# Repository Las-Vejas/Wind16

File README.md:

# Wind16
A 4x4 macropad, with backlit keys and a fully square design.

## Components

The macropad contains 16 keys, each backlit with an SK6812mini-e led. It is controlled by a Seeed XIAO RP2040 microcontroller using either kmk or qmk software.
The switches will be Gateron Milky Yellows as they feel magnificent. On them there will be white keycaps on which I will make vynil stickers for when I decide on the actions that the keys will be doing.

A lot of people on the HackClub Slack have been against my design, and how I have placed the Xiao. I myself think its a great design choice, that won’t interfere with any other component because, in theory with pin headers commonly being 2 mm tall, I should have enough clearance to fit my components on the top and bottom part of the pcb with just enough to spare so that the RP2040 wouldn’t be touching anything.

<br>

<br>

<br>

<br>

## BOM

| **Quantity** | **Item**                      | **Cost** | **Link**                                                                                                                                                                                                                                                                                                                                                                                                                                                                                                                                                                                                                             |
| ------------ | ----------------------------- | -------- | ------------------------------------------------------------------------------------------------------------------------------------------------------------------------------------------------------------------------------------------------------------------------------------------------------------------------------------------------------------------------------------------------------------------------------------------------------------------------------------------------------------------------------------------------------------------------------------------------------------------------------------ |
| 16           | Gateron Milky Yellow Switches | $8.32    | [Link](https://fr.aliexpress.com/item/1005006425450443.html?spm=a2g0o.cart.0.0.565438danX8OTX&mp=1&pdp_npi=5%40dis%21USD%21USD%208.32%21USD%208.32%21%21USD%208.32%21%21%21%40211b819117572797256232729e57a1%2112000037120671470%21ct%21LU%216401819456%21%211%210&gatewayAdapt=glo2fra) |
| 16           | Diodes SOD-123                | $1.56    | [Link](https://fr.aliexpress.com/item/1005001994794541.html?spm=a2g0o.order_detail.order_detail_item.3.e827f19ctnbrt6&gatewayAdapt=glo2fra) |
| 16           | SK6812mini-e Leds             | $3.33    | [Link](https://fr.aliexpress.com/item/1005003056797785.html?spm=a2g0o.detail.0.0.21a3YgQUYgQUyJ&mp=1&pdp_npi=5%40dis%21USD%21USD%204.76%21USD%203.33%21%21USD%203.26%21%21%21%40211b819117572793994331848e57a1%2112000023624298356%21ct%21LU%216401819456%21%211%210&_gl=1*wax1qx*_gcl_au*MTMyNTE0ODE3My4xNzUxNTY4NzEw*_ga*OTU2MTIwNzcxMDc0MTcyLjE3NTEwOTE0NzQ2NDg.*_ga_VED1YSGNC7*czE3NTcyNzkxNzkkbzQyJGcxJHQxNzU3Mjc5Mzk5JGo1JGwwJGgw&gatewayAdapt=glo2fra) |
| 1            | Seeed Xiao RP2040             | $8.75    | [Link](https://fr.aliexpress.com/item/1005003682505451.html?spm=a2g0o.productlist.main.1.29f17691lODYnp&algo_pvid=3de96513-9bd7-44e5-bd78-c8e1c5994e89&algo_exp_id=3de96513-9bd7-44e5-bd78-c8e1c5994e89-0&pdp_ext_f=%7B%22order%22%3A%2240%22%2C%22eval%22%3A%221%22%7D&pdp_npi=6%40dis%21EUR%217.28%214.52%21%21%218.30%215.15%21%402103868817572792142017471ef2af%2112000040089549450%21sea%21LU%216401819456%21X%211%210%21n_tag%3A-29912%3Bd%3A538c1a44%3Bm03_new_user%3A-29895&curPageLogUid=zx985QJAQOHJ&utparam-url=scene%3Asearch%7Cquery_from%3A%7Cx_object_id%3A1005003682505451%7C_p_origin_prod%3A&gatewayAdapt=glo2fra) |
| 16           | See-through keycaps           | $8.28    | [Link](https://fr.aliexpress.com/item/1005002976015114.html?spm=a2g0o.cart.0.0.59b138da7fjJ33&mp=1&pdp_npi=5%40dis%21USD%21USD%204.14%21USD%204.14%21%21USD%203.94%21%21%21%40211b876e17572803462205417e89b4%2112000023033844982%21ct%21LU%216401819456%21%212%210&gatewayAdapt=glo2fra) |
| 1            | 3D printed case               | N/A      | N/A  |                                                                                                                                                                                                                                                                                                                                                                                                                                                                                                                                                                                                                                
| 5            | M2 6mm Screws                 | $1.70    | [Link](https://www.aliexpress.com/item/1005004531602992.html?spm=a2g0o.cart.0.0.3b7738dao8IXAl&mp=1&pdp_npi=5%40dis%21USD%21USD%201.76%21USD%201.70%21%21USD%201.61%21%21%21%402103890917573922922277800e2784%2112000029499545502%21ct%21LU%216401819456%21%211%210&pdp_ext_f=%7B%22cart2PdpParams%22%3A%7B%22pdpBusinessMode%22%3A%22retail%22%7D%7D) |                                                                                                                                                                                                                                                                                                                                                                                                                                                                                                                                                                                                                                 | 5            | M2 8mm Standoffs              | $3.99    | [Link](https://www.aliexpress.com/item/32974970926.html?spm=a2g0o.cart.0.0.3b7738dao8IXAl&mp=1&pdp_npi=5%40dis%21USD%21USD%203.19%21USD%203.03%21%21USD%202.97%21%21%21%402103890917573923781348484e2784%2166700945881%21ct%21LU%216401819456%21%211%210) |
| 5            | M2 8mm Standoffs              | $3.30    | [Link](https://www.aliexpress.com/item/32974970926.html?spm=a2g0o.cart.0.0.f8e638daTMm8RF&mp=1&pdp_npi=5%40dis%21USD%21USD%203.19%21USD%203.03%21%21USD%203.03%21%21%21%402103835c17574519186483243e8d53%2166700945881%21ct%21LU%216401819456%21%211%210) |
| 5            | Rubber Bumpers (feet)         | $4.01    | [Link](https://fr.aliexpress.com/item/1005006259472984.html?spm=a2g0o.cart.0.0.3b7738dao8IXAl&mp=1&pdp_npi=5%40dis%21USD%21USD%202.77%21USD%202.77%21%21USD%202.77%21%21%21%402103890917573922922277800e2784%2112000036504769044%21ct%21LU%216401819456%21%211%210&gatewayAdapt=glo2fra) |

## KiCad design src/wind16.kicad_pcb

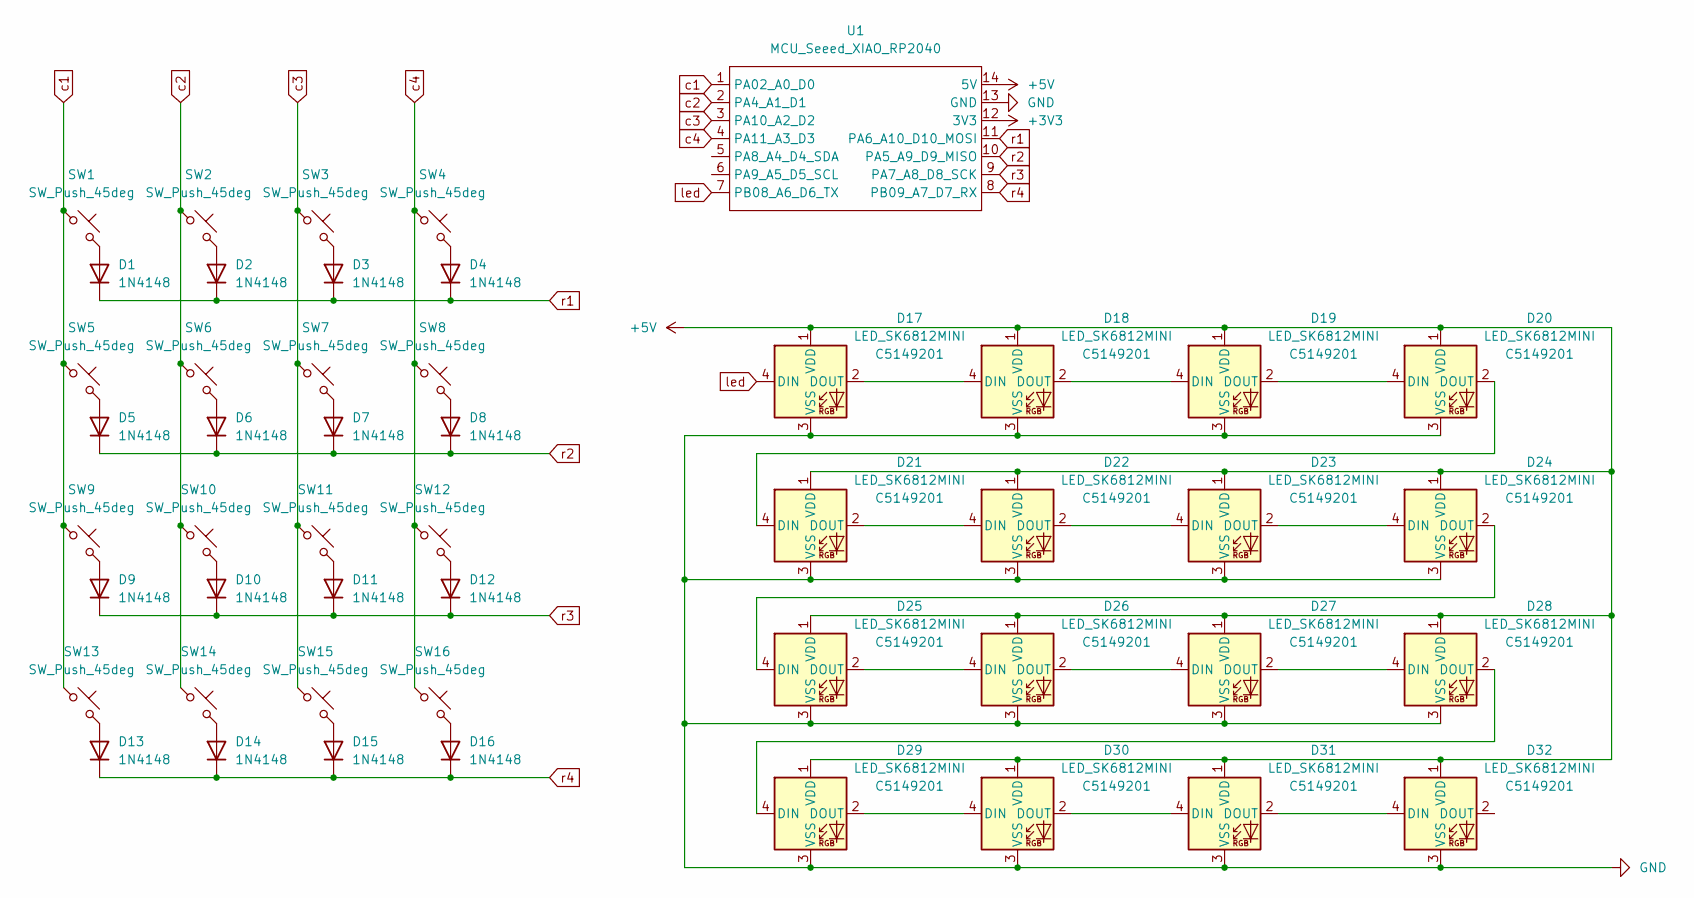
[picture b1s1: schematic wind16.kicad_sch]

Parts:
D1, D2, D3, D4, D5, D6, D7, D8, D9, D10, D11, D12, D13, D14, D15, D16: 1N4148; Diode_SOD-123
D17, D18, D19, D20, D21, D22, D23, D24, D25, D26, D27, D28, D29, D30, D31, D32: LED_SK6812MINI; LCSC C5149201
SW1: SW_Push_45deg; SW_Cherry_MX_1.00u_PCB
SW2, SW3, SW4, SW5, SW6, SW7, SW8, SW9, SW10, SW11, SW12, SW13, SW14, SW15, SW16: SW_Push_45deg; Hotswap_MX_1.00u
U1: MCU_Seeed_XIAO_RP2040; XIAO-RP2040-DIP

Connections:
+3V3: U1.12 (3V3)
+5V: D17.1 (VDD), D18.1 (VDD), D19.1 (VDD), D20.1 (VDD), D21.1 (VDD), D22.1 (VDD), D23.1 (VDD), D24.1 (VDD), D25.1 (VDD), D26.1 (VDD), D27.1 (VDD), D28.1 (VDD), D29.1 (VDD), D30.1 (VDD), D31.1 (VDD), D32.1 (VDD), U1.14 (5V)
GND: D17.3 (VSS), D18.3 (VSS), D19.3 (VSS), D20.3 (VSS), D21.3 (VSS), D22.3 (VSS), D23.3 (VSS), D24.3 (VSS), D25.3 (VSS), D26.3 (VSS), D27.3 (VSS), D28.3 (VSS), D29.3 (VSS), D30.3 (VSS), D31.3 (VSS), D32.3 (VSS), U1.13 (GND)
unnamed: D1.2 (A), SW1.2
unnamed: D2.2 (A), SW2.2
unnamed: D3.2 (A), SW3.2
unnamed: D4.2 (A), SW4.2
unnamed: D5.2 (A), SW5.2
unnamed: D6.2 (A), SW6.2
unnamed: D7.2 (A), SW7.2
unnamed: D8.2 (A), SW8.2
unnamed: D9.2 (A), SW9.2
unnamed: D10.2 (A), SW10.2
unnamed: D11.2 (A), SW11.2
unnamed: D12.2 (A), SW12.2
unnamed: D13.2 (A), SW13.2
unnamed: D14.2 (A), SW14.2
unnamed: D15.2 (A), SW15.2
unnamed: D16.2 (A), SW16.2
unnamed: D17.2 (DOUT), D18.4 (DIN)
unnamed: D18.2 (DOUT), D19.4 (DIN)
unnamed: D19.2 (DOUT), D20.4 (DIN)
unnamed: D20.2 (DOUT), D21.4 (DIN)
unnamed: D21.2 (DOUT), D22.4 (DIN)
unnamed: D22.2 (DOUT), D23.4 (DIN)
unnamed: D23.2 (DOUT), D24.4 (DIN)
unnamed: D24.2 (DOUT), D25.4 (DIN)
unnamed: D25.2 (DOUT), D26.4 (DIN)
unnamed: D26.2 (DOUT), D27.4 (DIN)
unnamed: D27.2 (DOUT), D28.4 (DIN)
unnamed: D28.2 (DOUT), D29.4 (DIN)
unnamed: D29.2 (DOUT), D30.4 (DIN)
unnamed: D30.2 (DOUT), D31.4 (DIN)
unnamed: D31.2 (DOUT), D32.4 (DIN)
c1: SW1.1, SW5.1, SW9.1, SW13.1, U1.1 (PA02_A0_D0)
c2: SW2.1, SW6.1, SW10.1, SW14.1, U1.2 (PA4_A1_D1)
c3: SW3.1, SW7.1, SW11.1, SW15.1, U1.3 (PA10_A2_D2)
c4: SW4.1, SW8.1, SW12.1, SW16.1, U1.4 (PA11_A3_D3)
led: D17.4 (DIN), U1.7 (PB08_A6_D6_TX)
r1: D1.1 (K), D2.1 (K), D3.1 (K), D4.1 (K), U1.11 (PA6_A10_D10_MOSI)
r2: D5.1 (K), D6.1 (K), D7.1 (K), D8.1 (K), U1.10 (PA5_A9_D9_MISO)
r3: D9.1 (K), D10.1 (K), D11.1 (K), D12.1 (K), U1.9 (PA7_A8_D8_SCK)
r4: D13.1 (K), D14.1 (K), D15.1 (K), D16.1 (K), U1.8 (PB09_A7_D7_RX)

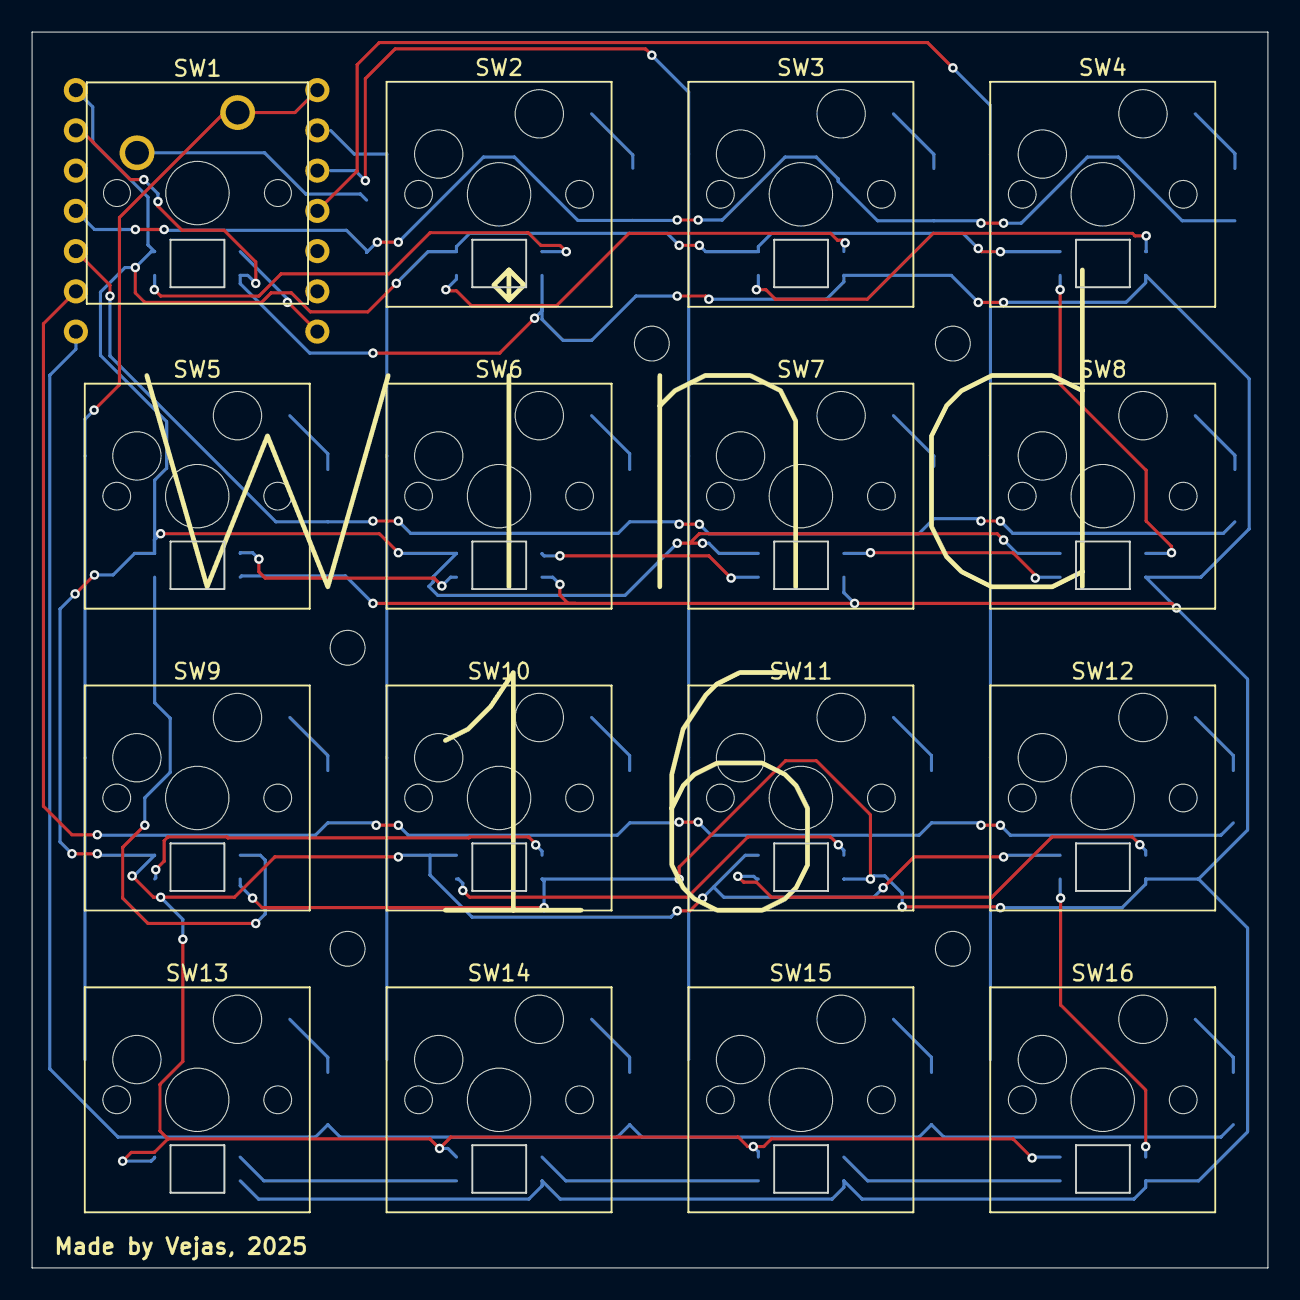
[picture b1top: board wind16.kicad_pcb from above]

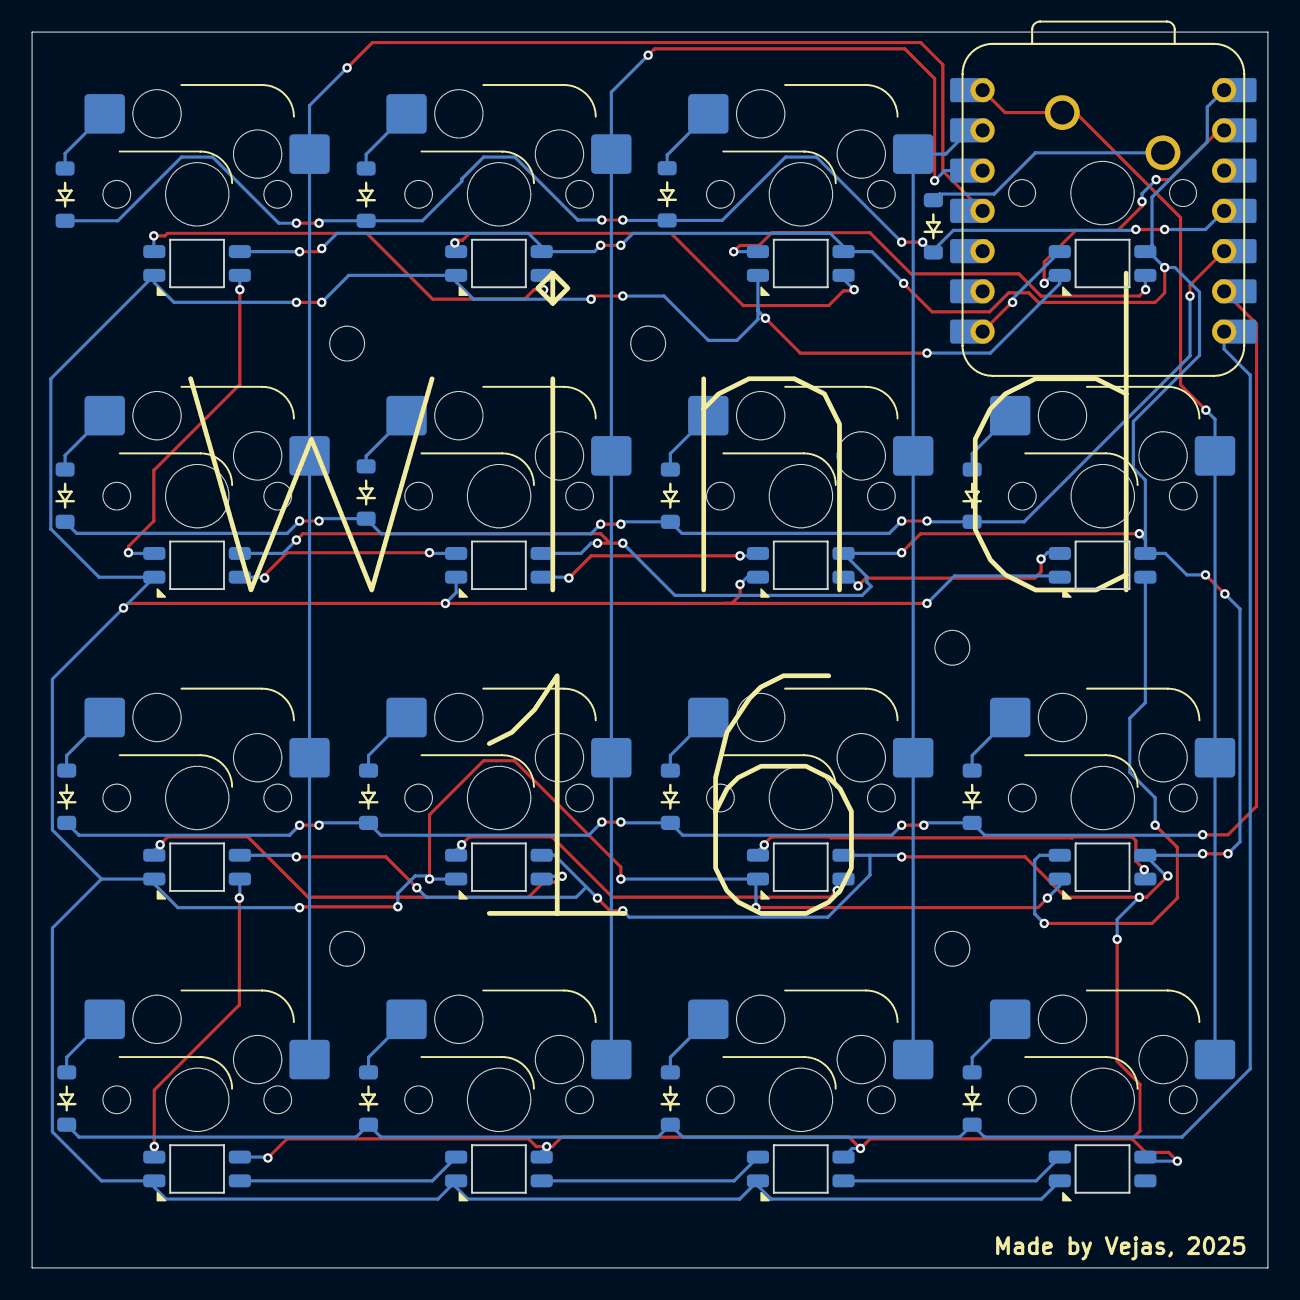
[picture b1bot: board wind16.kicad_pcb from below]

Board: 2 copper layers, 78.0 x 78.0 mm, 49 parts (33 on the bottom side), 42 nets.

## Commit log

2025-09-06 init
2025-09-06 added journal
2025-09-07 added images
2025-09-07 stuff 1.2
2025-09-07 Update JOURNAL.md
    png not jpg
2025-09-07 journal
2025-09-07 added bom
2025-09-09 loads of shit 1.3
2025-09-09 update bom
2025-09-09 gerbers, jlc, small changes
2025-09-09 gerbs
2025-09-09 jlc cart
